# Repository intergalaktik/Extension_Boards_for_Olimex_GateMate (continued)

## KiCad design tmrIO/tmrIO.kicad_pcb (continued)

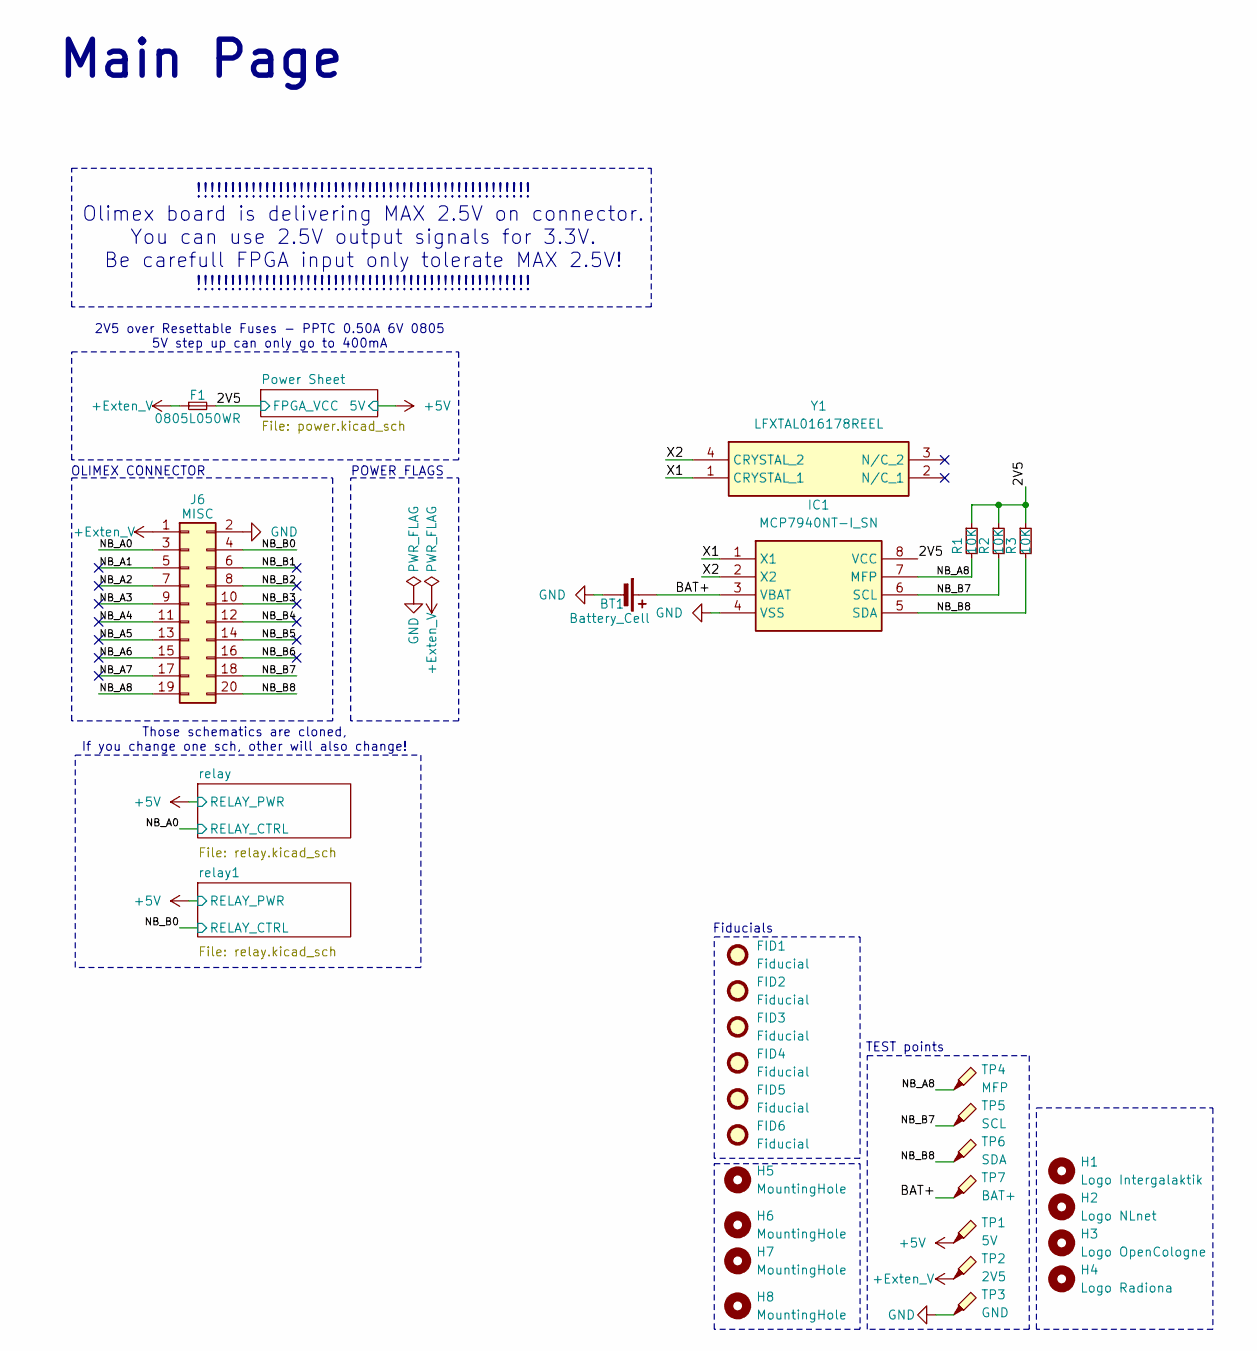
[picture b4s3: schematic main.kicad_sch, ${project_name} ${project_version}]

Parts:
BT1: Battery_Cell; BatteryHolder_Keystone_2998_1x6.8mm
F1: 0805L050WR; Fuse_0805_2012Metric
FID1, FID2, FID3, FID4, FID5, FID6: Fiducial; Fiducial_0.5mm_Mask1mm
H1: Logo Intergalaktik; intergalaktik
H2: Logo NLnet; nlnet
H3: Logo OpenCologne; open_cologne_small
H4: Logo Radiona; radiona_small
H5, H6, H7, H8: MountingHole; MountingHole_2.2mm_M2
IC1: MCP7940NT-I_SN; SOIC127P600X175-8N; Mouser Part Number 579-MCP7940NT-I/SN
J6: MISC; PinSocket_2x10_P2.54mm_Vertical_SMD
R1, R2, R3: 10K; R_0402_1005Metric; MPN RC0603FR-071K1L; Mouser 603-RC0603FR-071K1L
TP1: 5V; TestPoint_Pad_D1.0mm
TP2: 2V5; TestPoint_Pad_D1.0mm
TP3: GND; TestPoint_Pad_D1.0mm
TP4: MFP; TestPoint_Pad_D1.0mm
TP5: SCL; TestPoint_Pad_D1.0mm
TP6: SDA; TestPoint_Pad_D1.0mm
TP7: BAT+; TestPoint_Pad_D1.0mm
Y1: LFXTAL016178REEL; Mouser Part Number 449-LFXTAL016178REEL

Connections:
+5V: TP1.1; also elsewhere on the board
+Exten_V: F1.1, J6.1, TP2.1
/Main Sheet/2V5: F1.2, IC1.8 (VCC), R1.1, R2.1, R3.1; also elsewhere on the board
/Main Sheet/BAT+: BT1.1 (+), IC1.3 (VBAT), TP7.1
/Main Sheet/NB_A0: J6.3; also elsewhere on the board
/Main Sheet/NB_A1: J6.5
/Main Sheet/NB_A2: J6.7
/Main Sheet/NB_A3: J6.9
/Main Sheet/NB_A4: J6.11
/Main Sheet/NB_A5: J6.13
/Main Sheet/NB_A6: J6.15
/Main Sheet/NB_A7: J6.17
/Main Sheet/NB_A8: IC1.7 (MFP), J6.19, R1.2, TP4.1
/Main Sheet/NB_B0: J6.4; also elsewhere on the board
/Main Sheet/NB_B1: J6.6
/Main Sheet/NB_B2: J6.8
/Main Sheet/NB_B3: J6.10
/Main Sheet/NB_B4: J6.12
/Main Sheet/NB_B5: J6.14
/Main Sheet/NB_B6: J6.16
/Main Sheet/NB_B7: IC1.6 (SCL), J6.18, R2.2, TP5.1
/Main Sheet/NB_B8: IC1.5 (SDA), J6.20, R3.2, TP6.1
/Main Sheet/X1: IC1.1 (X1), Y1.1 (CRYSTAL_1)
/Main Sheet/X2: IC1.2 (X2), Y1.4 (CRYSTAL_2)
GND: BT1.2 (-), IC1.4 (VSS), J6.2, TP3.1; also elsewhere on the board

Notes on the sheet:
POWER FLAGS
Fiducials
!!!!!!!!!!!!!!!!!!!!!!!!!!!!!!!!!!!!!!!!!!!!!!!!! Olimex board is delivering MAX 2.5V on connector. You can use 2.5V output signals for 3.3V. Be carefull FPGA input only tolerate MAX 2.5V! !!!!!!!!!!!!!!!!!!!!!!!!!!!!!!!!!!!!!!!!!!!!!!!!!
Those schematics are cloned, If you change one sch, other will also change!
TEST points
OLIMEX CONNECTOR
2V5 over Resettable Fuses - PPTC 0.50A 6V 0805 5V step up can only go to 400mA
Main Page

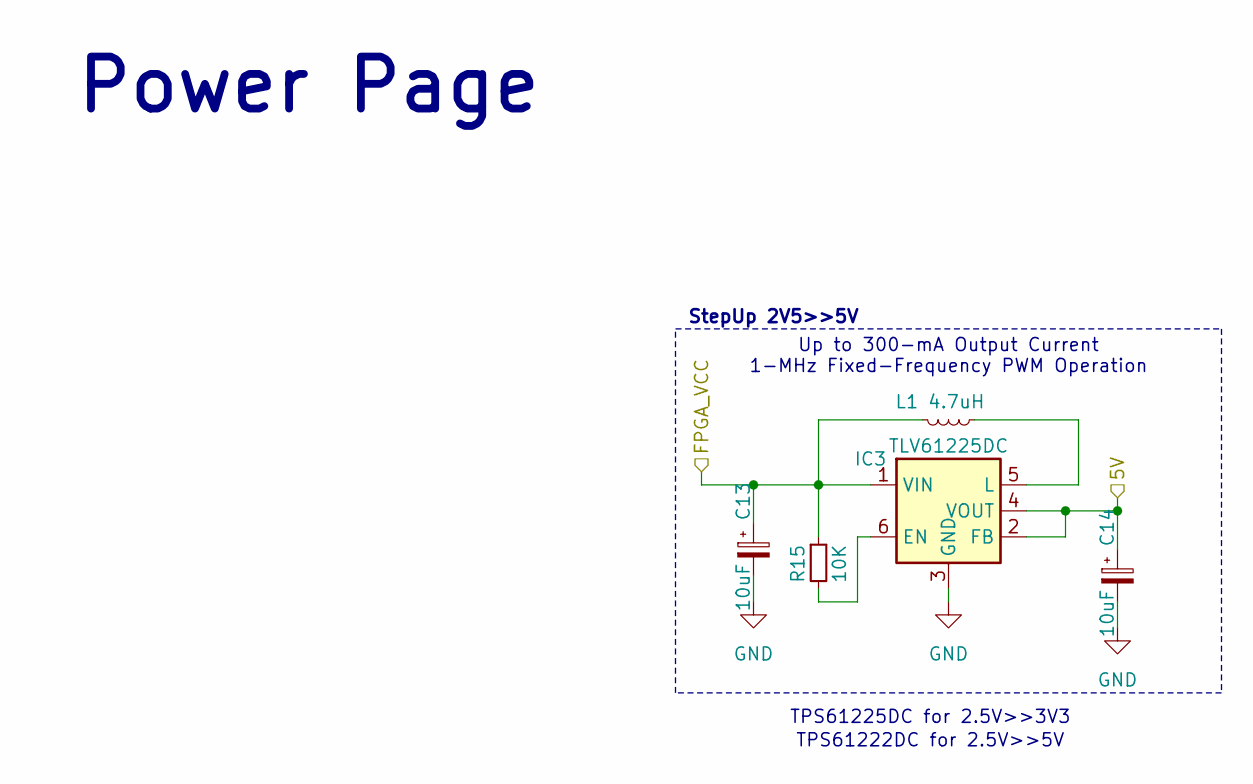
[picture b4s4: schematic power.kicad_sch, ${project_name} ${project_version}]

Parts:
C13, C14: 10uF; C_0603_1608Metric
IC3: TLV61225DC; SOT-363_SC-70-6
L1: 4.7uH; L_0603_1608Metric
R15: 10K; R_0402_1005Metric; MPN RC0603FR-071K1L; Mouser 603-RC0603FR-071K1L

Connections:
+5V: C14.1, IC3.2 (FB), IC3.4 (VOUT); also elsewhere on the board
/Main Sheet/2V5: C13.1, IC3.1 (VIN), L1.2, R15.1; also elsewhere on the board
GND: C13.2, C14.2, IC3.3 (GND); also elsewhere on the board
unnamed: IC3.6 (EN), R15.2
unnamed: IC3.5 (L), L1.1

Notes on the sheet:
Power Page
StepUp 2V5>>5V
Up to 300-mA Output Current 1-MHz Fixed-Frequency PWM Operation
TPS61222DC for 2.5V>>5V
TPS61225DC for 2.5V>>3V3

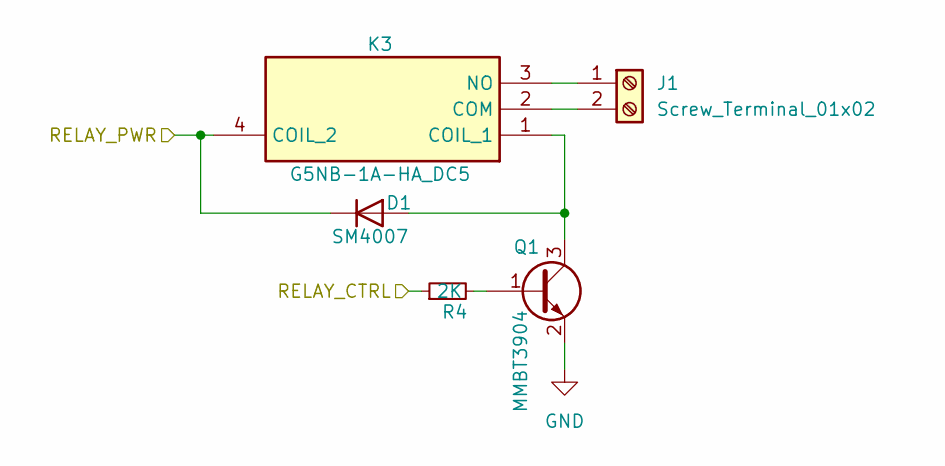
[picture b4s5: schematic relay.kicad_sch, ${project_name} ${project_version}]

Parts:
D1: SM4007; D_MELF
J1: Screw_Terminal_01x02; TerminalBlock_Phoenix_PT-1,5-2-3.5-H_1x02_P3.50mm_Horizontal
K3: G5NB-1A-HA_DC5; G5NB1AHADC5; Mouser Part Number 653-G5NB-1A-HADC5
Q1: MMBT3904; SOT-23
R4: 2K; R_0402_1005Metric; MPN RC0603FR-071K1L; Mouser 603-RC0603FR-071K1L

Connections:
+5V: D1.1 (K), K3.4 (COIL_2); also elsewhere on the board
/Main Sheet/NB_A0: R4.1; also elsewhere on the board
GND: Q1.2 (E); also elsewhere on the board
unnamed: D1.2 (A), K3.1 (COIL_1), Q1.3 (C)
unnamed: J1.1, K3.3 (NO)
unnamed: J1.2, K3.2 (COM)
unnamed: Q1.1 (B), R4.2

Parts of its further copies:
D2: SM4007; D_MELF
J4: Screw_Terminal_01x02; TerminalBlock_Phoenix_PT-1,5-2-3.5-H_1x02_P3.50mm_Horizontal
K4: G5NB-1A-HA_DC5; G5NB1AHADC5; Mouser Part Number 653-G5NB-1A-HADC5
Q2: MMBT3904; SOT-23
R5: 2K; R_0402_1005Metric; MPN RC0603FR-071K1L; Mouser 603-RC0603FR-071K1L

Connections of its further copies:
+5V: D2.1 (K), K4.4 (COIL_2); also elsewhere on the board
/Main Sheet/NB_B0: R5.1; also elsewhere on the board
GND: Q2.2 (E); also elsewhere on the board
unnamed: D2.2 (A), K4.1 (COIL_1), Q2.3 (C)
unnamed: J4.1, K4.3 (NO)
unnamed: J4.2, K4.2 (COM)
unnamed: Q2.1 (B), R5.2

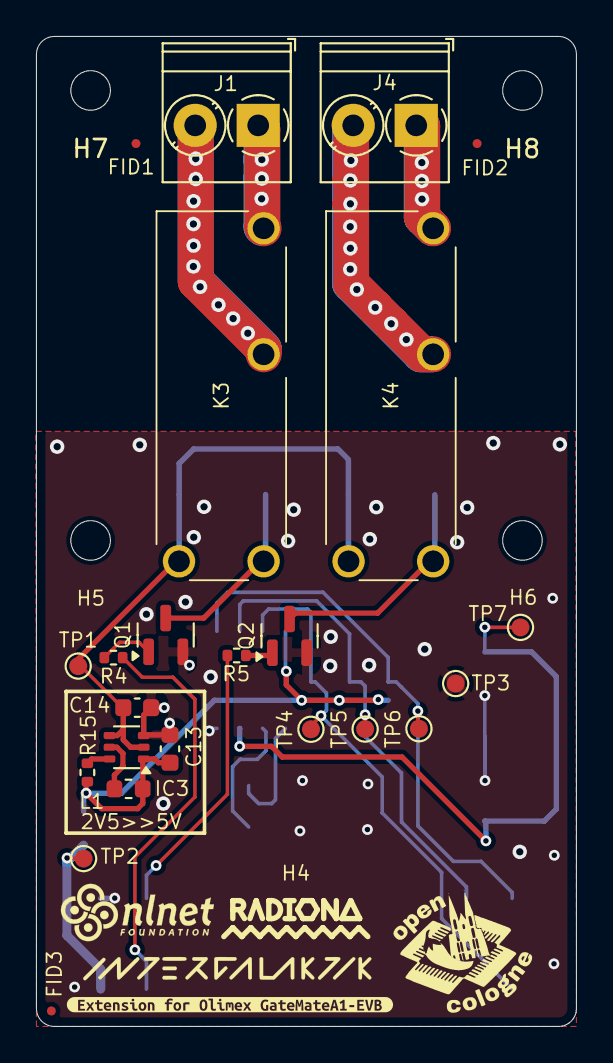
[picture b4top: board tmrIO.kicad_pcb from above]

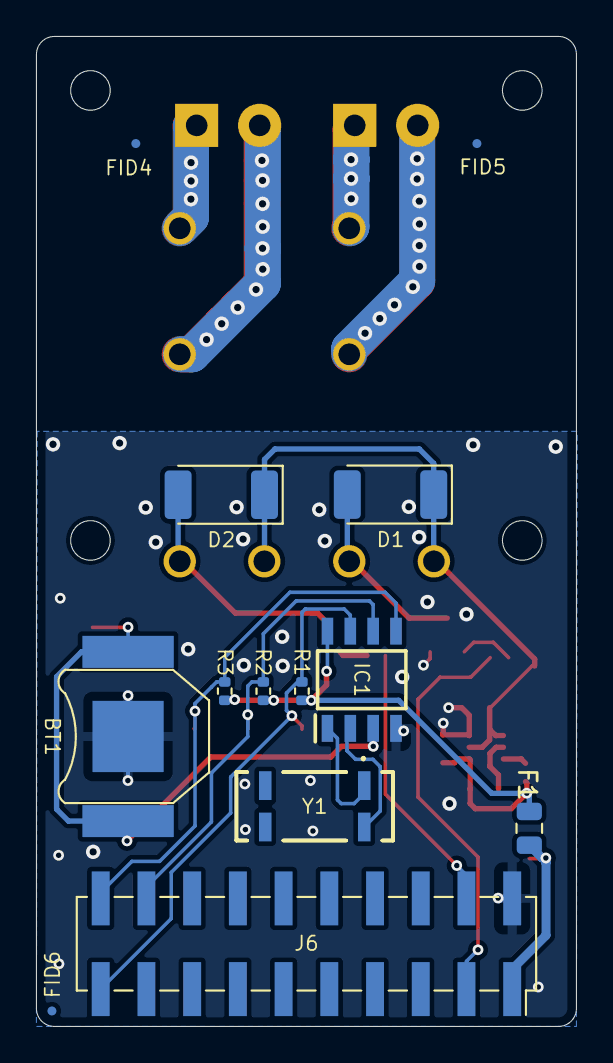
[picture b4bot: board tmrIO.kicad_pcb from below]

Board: 4 copper layers, 30.0 x 55.0 mm, 45 parts (13 on the bottom side), 22 nets.

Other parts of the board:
kibuzzard-674D68C8: G***; kibuzzard-674D68C8
